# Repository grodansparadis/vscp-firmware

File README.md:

# VCSP Firmware

VSCP firmware contains examples for different hardware architectures of how to
implement the Very Simple Control Protocol (VSCP, [http://www.vscp.org](http://www.vscp.org)).

Shared VSCP firmware files reside in `/src`, while architecture-specific
common files reside in `/{arch}/common`.

Most important files for implementers are:

  * /src/vscp-firmware.* (for Level I nodes) and
  * /src/vscp-firmware-level2.* (for Level II (and Level I) nodes)

which both implements the VSCP protocol. The first alternative is created for very space limited devices, the second is for devices with more normal resources. 

There are also some references to
vscp_class.h and vscp_type.h which reside in the vscp_software repository
in the path /src/vscp/common. It is preferred to include these files from
that second repository (and not to make redundant copies if possible).

Documentation on how to build your own nodes from this code is [here](https://grodansparadis.github.io/vscp-doc-firmware/#/) 

Local module documentation for the helper library is available in [docs/vscp-firmware-helper.md](docs/vscp-firmware-helper.md).
Local module documentation for the VSCP FIFO helper is available in [docs/vscp-fifo.md](docs/vscp-fifo.md).
Local module documentation for the Level I firmware core is available in [docs/vscp-firmware.md](docs/vscp-firmware.md).
Local module documentation for the AES module is available in [docs/vscp-aes.md](docs/vscp-aes.md).
Local module documentation for the Level II firmware framework is available in [docs/vscp-firmware-level2.md](docs/vscp-firmware-level2.md).
Local module documentation for the VSCP link protocol is available in [docs/vscp-link-protocol.md](docs/vscp-link-protocol.md).
Local module documentation for serial protocol definitions is available in [docs/vscp-serial.md](docs/vscp-serial.md).
Local module documentation for the bootloader is available in [docs/vscp-bootloader.md](docs/vscp-bootloader.md).
Host-side firmware update flow for bootloader integration is available in [docs/vscp-bootloader-host-sequence.md](docs/vscp-bootloader-host-sequence.md).
Reusable VSCP link protocol callback bring-up checklist is available in [docs/examples/vscp-link-protocol-callback-checklist.md](docs/examples/vscp-link-protocol-callback-checklist.md).
Reusable VSCP Level I firmware porting checklist is available in [docs/examples/vscp-firmware-porting-checklist.md](docs/examples/vscp-firmware-porting-checklist.md).

## Recent updates

- Added `vscp_fwhlp_parseStringValue` behavior notes in [docs/vscp-firmware-helper.md](docs/vscp-firmware-helper.md), including base-prefix handling (`0x`, `0`, `0b`) and `endptr` token parsing semantics.

## Version

The library version is `year.month.patch` (for example `26.11.3`) and is in
[src/vscp-firmware-version.h](src/vscp-firmware-version.h):

- `VSCP_FIRMWARE_LIB_VERSION_YEAR`, `_MONTH`, `_PATCH` and `_STR`
- `VSCP_FIRMWARE_LIB_VERSION` as one number for compile time checks, e.g.
  `#if VSCP_FIRMWARE_LIB_VERSION >= VSCP_FIRMWARE_LIB_VERSION_CODE(26, 11, 3)`

It is updated automatically on every push to `master` by the
[Update version](https://github.com/grodansparadis/vscp-firmware/actions/workflows/update-version.yml)
workflow: the patch number counts the pushes in a month and starts at 0 in a
new month. Do not edit the header by hand. Pushes whose commit message
contains `[skip ci]` (anywhere, also in the body) do not change the version;
the workflow can also be started by hand from the Actions tab.

This is the version of the library code, not the VSCP protocol version that
nodes report in registers 0x81/0x82 (`VSCP_MAJOR_VERSION` etc. in
`vscp-firmware.h`).

## CI

- Tests workflow: [GitHub Actions - Tests](https://github.com/grodansparadis/vscp-firmware/actions/workflows/tests.yml)
- Version workflow: [GitHub Actions - Update version](https://github.com/grodansparadis/vscp-firmware/actions/workflows/update-version.yml)
- Latest workflow runs: [GitHub Actions runs](https://github.com/grodansparadis/vscp-firmware/actions)

The main reference implementations for VSCP over CAN is the Paris and the Kelvin modules. Both can found [here](http://www.grodansparadis.com/products.html) along with other open source products. All modules are available as 
ready made modules, bare pcb's and software and hardware is and will always be fully open and free. All design documents are open and available.

## License

The whole source code is published under the MIT license. Consider the different licenses of possible third party libraries too!

## Contribution

Unless you explicitly state otherwise, any contribution intentionally submitted for inclusion in the work by you, shall be licensed as above, without any additional terms or conditions.

Copyright 2000-2026 Ake Hedman <akhe@grodansparadis.com>, <a href="http://www.grodansparadis.com">Grodans Paradis AB</a>

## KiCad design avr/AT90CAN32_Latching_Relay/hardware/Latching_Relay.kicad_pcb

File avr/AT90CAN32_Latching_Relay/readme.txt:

This project implements a latchnig relay draive on an Atmega AT90CAN32 device. 

Pulse is sent after receiving Open (0x03) or Close (0x04) event.

Code is built using the GCC (AVR GCC) compiler.

Project configurations are done in the file vscp_projdefs.h  Also paths to include folders is 
in the Makefile and you probably have to change the paths.

If you port this project to use another compiler please use the vscp_compiler.h header to add 
compiler specific stuff. This file and the vscp_projdefs.h should be included in every file
of the project.

The mdf file describes the VSCP functionality.

SW0 - Init button. Press to initiate node and start nickname process.

LED0 - Status LED. Will blink during init process, stays steady on during operation.  

Serial channel, 38400-8N1 is used for debug messages.

Decision matrix is implemented.
No rows in the DM

Actions
=======
0x00 - No operation.

More information to be found at http://www.vscp.org/wiki/doku.php/modules/atmel_temp_humid

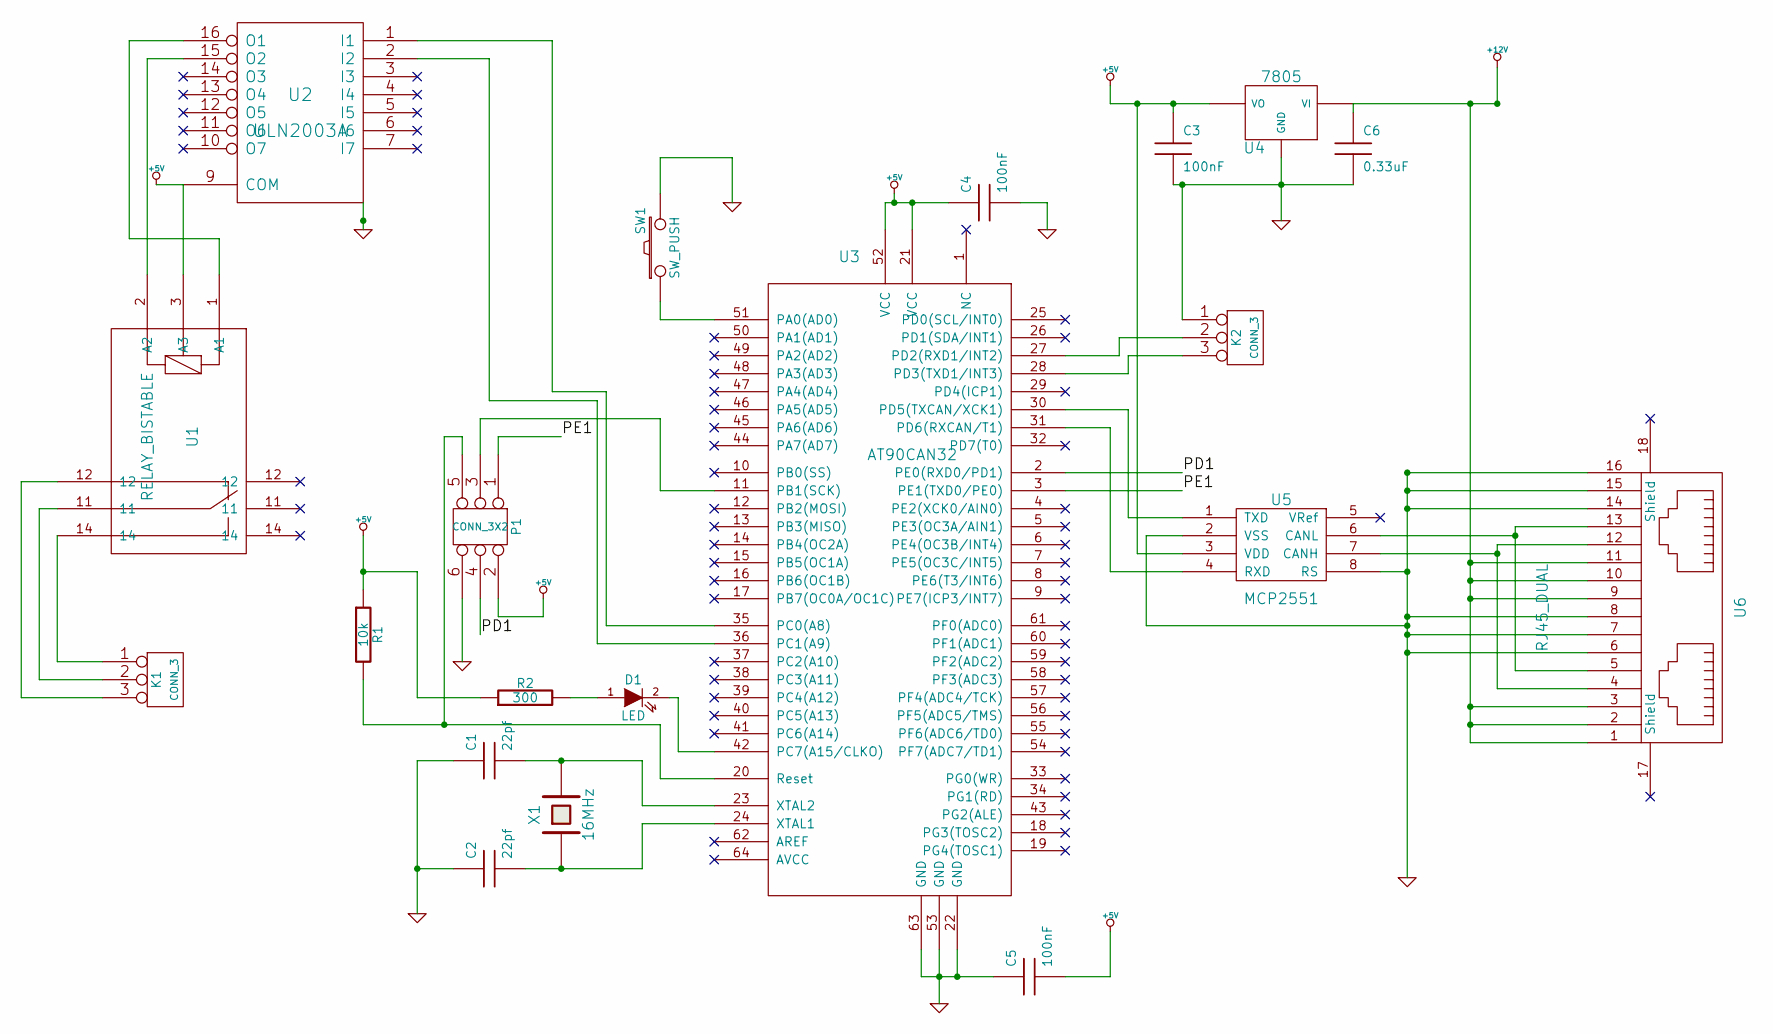
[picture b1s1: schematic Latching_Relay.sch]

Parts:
C1, C2: 22pf
C3, C4, C5: 100nF
C6: 0.33uF
D1: LED
K1, K2: CONN_3
P1: CONN_3X2
R1: 10k
R2: 300
SW1: SW_PUSH
U1: RELAY_BISTABLE
U2: ULN2003A
U3: AT90CAN32
U4: 7805
U5: MCP2551
U6: RJ45_DUAL
X1: 16MHz

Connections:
+5V: C3.1, C4.1, C5.2, P1.2, R1.1, R2.1, U1.3 (A3), U2.9 (COM), U3.21 (VCC), U3.52 (VCC), U4.3 (VO), U5.3 (VDD)
+12V: C6.1, U4.1 (VI), U6.1, U6.2, U6.3, U6.9, U6.10, U6.11
/PD1: P1.4, U3.2 (PE0(RXD0/PD1))
/PE1: P1.1, U3.3 (PE1(TXD0/PE0))
GND: C1.1, C2.1, C3.2, C4.2, C5.1, C6.2, K2.1, P1.6, SW1.2, U2.8 (GND), U3.22 (GND), U3.53 (GND), U3.63 (GND), U4.2 (GND), U5.2 (VSS), U5.8 (RS), U6.6, U6.7, U6.8, U6.14, U6.15, U6.16
unnamed: K2.2 (PM), U3.27 (PD2(RXD1/INT2))
unnamed: K2.3, U3.28 (PD3(TXD1/INT3))
unnamed: SW1.1, U3.51 (PA0(AD0))
unnamed: D1.2 (K), U3.42 (PC7(A15/CLKO))
unnamed: U3.30 (PD5(TXCAN/XCK1)), U5.1 (TXD)
unnamed: U3.31 (PD6(RXCAN/T1)), U5.4 (RXD)
unnamed: P1.3, U3.11 (PB1(SCK))
unnamed: P1.5, R1.2, U3.20 (Reset)
unnamed: U2.2 (I2), U3.36 (PC1(A9))
unnamed: U2.1 (I1), U3.35 (PC0(A8))
unnamed: K1.1, U1.14
unnamed: U1.1 (A1), U2.16 (O1)
unnamed: U1.2 (A2), U2.15 (O2)
unnamed: U5.6 (CANL), U6.5, U6.13
unnamed: U5.7 (CANH), U6.4, U6.12
unnamed: K1.3, U1.12
unnamed: K1.2 (PM), U1.11
unnamed: C1.2, U3.23 (XTAL2), X1.2
unnamed: C2.2, U3.24 (XTAL1), X1.1
unnamed: D1.1 (A), R2.2

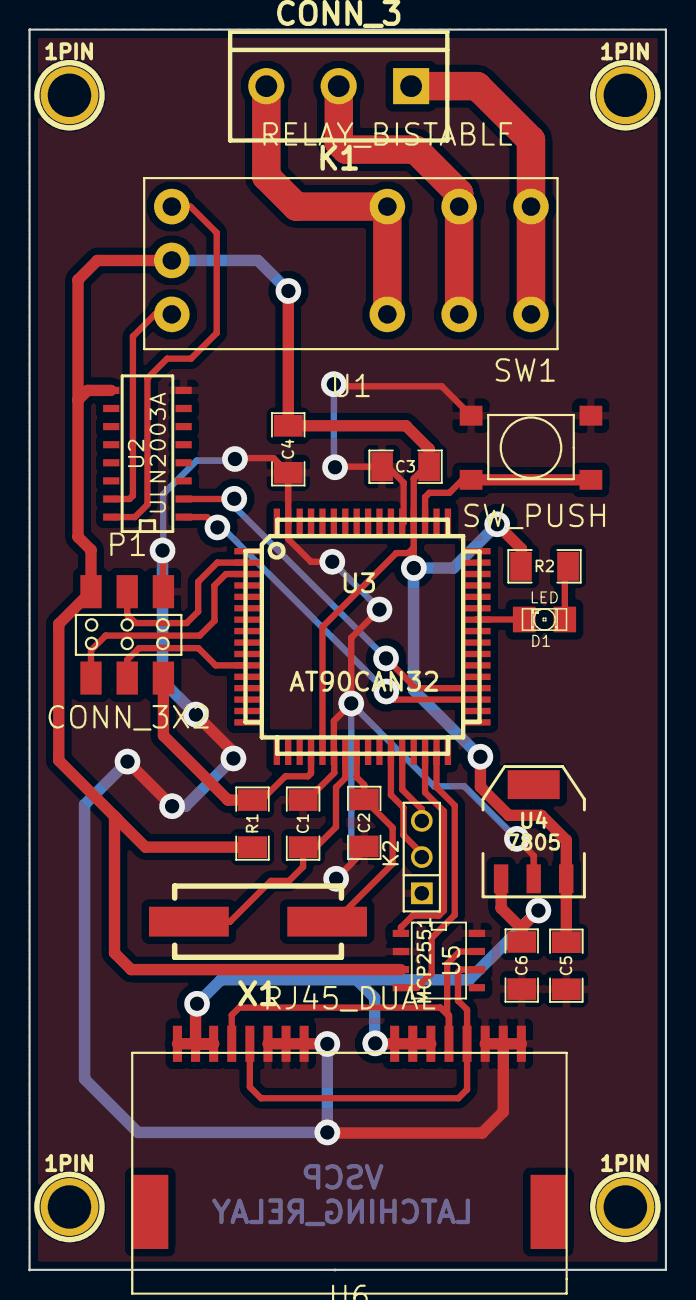
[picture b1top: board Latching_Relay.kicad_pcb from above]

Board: 2 copper layers, 44.7 x 87.1 mm, 24 parts (0 on the bottom side), 25 nets.

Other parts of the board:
1PIN, 1PIN#2, 1PIN#3, 1PIN#4: P***; 1pin

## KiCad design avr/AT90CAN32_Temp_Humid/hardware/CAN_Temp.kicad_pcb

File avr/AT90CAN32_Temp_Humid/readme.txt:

This project implements a temperature and a humidity sensor on an Atmega AT90CAN32device. 

Temperature and humidity are sent on a regular interval on the bus, the interval is set by the user using two registers.

Code is built using the GCC (AVR GCC) compiler.

Project configurations are done in the file vscp_projdefs.h  Also paths to include folders is 
in the Makefile and you probably have to change the paths.

If you port this project to use another compiler please use the vscp_compiler.h header to add 
compiler specific stuff. This file and the vscp_projdefs.h should be included in every file
of the project.

The mdf file describes the VSCP functionality.

SW0 - Init button. Press to initiate node and start nickname process.

LED0 - Status LED. Will blink during init process, stays steady on during operation.  

Serial channel, 38400-8N1 is used for debug messages.

Decision matrix is implemented.
No rows in the DM

Actions
=======
0x00 - No operation.

More information to be found at http://www.vscp.org/wiki/doku.php/modules/atmel_temp_humid

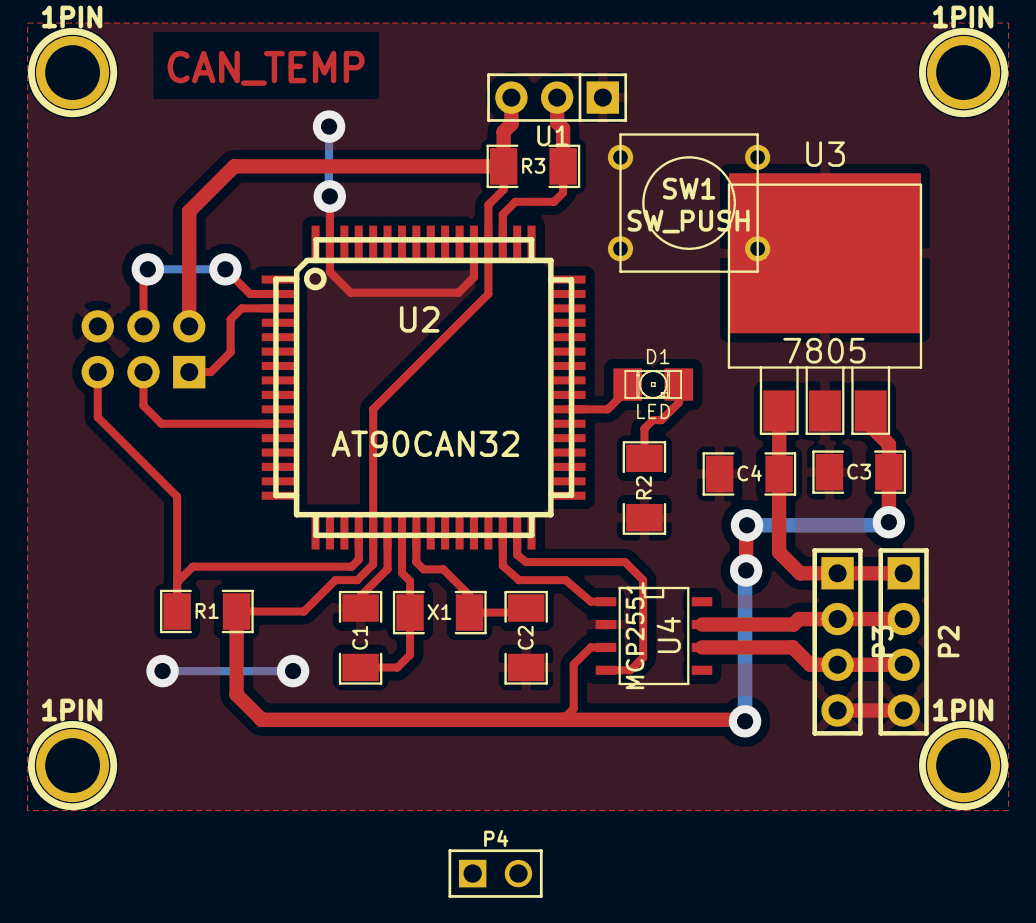
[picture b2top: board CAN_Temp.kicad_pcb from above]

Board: 2 copper layers, 22 parts (1 on the bottom side), 19 nets.

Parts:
1PIN, 1PIN#2, 1PIN#3, 1PIN#4: P***; 1pin
C1, C2: 22pf; SM1206
C3: 100nF; SM1206
C4: 0.33uF; SM1206
D1: LED; LED-1206
P1: CONN_3X2; pin_array_3x2
P2, P3: CONN_4; PIN_ARRAY_4x1
P4: CONN_2; PIN_ARRAY_2X1
R1: 10k; SM1206
R2: 300; SM1206
R3: 470k; SM1206
SW1: SW_PUSH; SW_PUSH_SMALL
U1: DS1820; PIN_ARRAY_3X1
U2: AT90CAN32; TQFP64_08
U3: 7805; DPAK3
U4: MCP2551; SO8E
X1: 16MHz; SM1206

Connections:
+5V: C3.1, P1.2, R1.1, R2.1, R3.1, U1.3, U2.21, U2.52, U3.3, U4.3
+12V: C4.1, P2.1, P3.1, U3.1
/PD1: P1.4, U2.2
/PE1: P1.1, U2.3
GND: C1.1, C2.1, C3.2, C4.2, P1.6, P2.4, P3.4, SW1.2, U1.1, U2.22, U2.53, U2.63, U3.2, U4.2, U4.8
unnamed: U2.30, U4.1
unnamed: U2.31, U4.4
unnamed: P1.3, U2.11
unnamed: P1.5, R1.2, U2.20
unnamed: P2.2, P3.2, U4.7
unnamed: P4.2, U2.28
unnamed: D1.2, R2.2
unnamed: P4.1, U2.27
unnamed: D1.1, U2.10
unnamed: R3.2, U1.2, U2.35
unnamed: SW1.1, U2.51
unnamed: P2.3, P3.3, U4.6
unnamed: C1.2, U2.23, X1.2
unnamed: C2.2, U2.24, X1.1

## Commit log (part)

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2015-03-23 Adding relay status register
2015-03-24 Cosmetics
2015-03-25 Preparing hardware
2015-04-01 Node now returns ON or OFF information event when state change instead of writing a register
2015-04-02 Fixed problem in read standard registers reported by Kim Portman. The device codes where at placed in thewrite routine instead of the read. Also a range check is done on mdf read suggested by Kim
2015-04-07 testing push from the office
2015-04-14 Change normalizer to fullfill latest change in WORKS
2015-04-15 Change vscp_goBootloaderMode() to fullfill latest change in WORKS
2015-05-21 Added CCITT CRC code
2015-05-21 Added crc8 routines Added fifo routines
2015-05-21 Added duplicates of critical files so there is no need to check out the full vscp_software repository. Needed for freertos work.
2015-05-21 Fixed some editing before IBM review
2015-05-22 commit before pull
2015-05-24 Synced with VSCP software - New classes CLASS1.ERROR/CLASS1.DIAGNOSTIC plus added event
2015-05-25 Anti-debounce for input
2015-05-25 Updated VSCP type copy
2015-05-28 Added support to PIC18F4580 and possibility of multiple BRG configuration selected using _XTAL_FREQ definition
2015-05-28 New projects
2015-05-28 Reverted class and type files that are just copies here.
2015-05-28 Spelling
2015-05-28 Restored missing files
2015-05-28 Trying to fix sendVSCPFrame
2015-06-11 Converted to new AVR studio
2015-06-12 Fixed extended read register response
2015-06-17 avr demo demo_vscp_node_can128 nw moved to avr studio
2015-06-17 Added link to demo hex
2015-06-17 changed the priority for packet bursts to the lowest priority (CAN == 111) so other frames win arbitration when they are sent. This will help other events moving on the bus.
2015-06-17 updated digiprobe project to compile with latest repository version
2015-07-09 Added VSCP_TYPE_DATA_COUNT
2015-09-10 Added
    Class=1060 (0x424) Measurement float
    and missing
    Class=1040 (0x410) Measurement string
2015-10-08 Added timstamp frames to serial protocol
2015-10-08 Added latest copy of common files
2015-10-14 cleanup
2015-10-20 Syncing headers
2015-10-21 Added CLASS2.PROTOCOL, Type=20 (0x14) High end server capabilities == synced with vscp repository
2015-10-26 Added 128-bit AES tiny code
2015-11-03 Synced includes
2015-11-09 Added code to read chip id on pic18
2015-11-25 Rolled back vscp_firmware.c/h from some happy hacking ;-) @SvenZ80
2015-11-25 Added macros to construct signed integers from EEPROM content in a safe c standard way.
2016-01-07 Removed segment check
2016-01-29 Fixed trillons of TAB's
2016-01-29 Added some untracked stuff
2016-02-03 Changed avr_can128 sample so it works with latest firmware
2016-02-03 Rnemamed local inttypes.h vscp_inttypes.h *** This file is usually not needed anymore ***
2016-02-04 Added initial lib for AVR1 bootloader
2016-02-07 New bootloader implemention for AVR
2016-02-07 Fixed problem in 32-bit macros
2016-02-12 Syncing
2016-03-02 Made work in progress firmware intrim. usable
2016-03-18 Added new internal calculation event
2016-03-23 Added error event and logger event
2016-03-23 Added history file to keep track of changes from now on
2016-03-23 Release 1.6.1
2016-09-06 update
    methods.c/.h updated to remain compatible with common/vscp_firmware.h
2016-09-06 avoid bus flooding
    added timer to avoid to dump to much events on bus
2016-12-09 rollout 2016
2016-12-29 Added event for sound level and sound pressure
2016-12-29 Synced types
2017-01-22 8bit -> 16bit eeprom adress
    bug preventing to read/write more than 128 eeprom locations
2017-01-22 add nickname accepted after setnickname event
    upp untik now, no response was send after setnickname event
2017-01-24 Sync with main
2017-02-02 aaboot
2017-02-02 cleaning up
2017-02-17 bootloader now works according to vscp-algorithm
    used to test bootloader firmware.
2017-02-17 added MDF
2017-04-05 HW-upgrade AAMEGA
    AAMEGA now has 32 output (instead of 16) with added piggyback-board
2017-04-13 The VSCP frame now have a full date/time field. Code that relay on the struct size must be recompiled.
2017-04-18 VSCP structure and frame now have a date/time block.
2017-05-08 Synced with the VSCP project
2017-06-13 Updated mu.ticast/udp constants
2017-06-14 USP and multicast frames was missing the century byte of the year.
2017-06-25 Updated to latest upstream version
2017-07-04 coap and mqtt removed fom capabilities word
2017-07-04 multicast moved
2017-07-11 vscpEvenEx had wrong size for head
2017-09-07 debug timerroutine
    only timer could be used from DM
2017-09-07 minor cleanup
2017-11-10 small update
    tweaked some timing: slower but more reliable
2017-11-10 shutters added
    added action-routines to drive shutter/blinds/...
2018-02-09 Sunced files with main
2018-02-19 Started work with Level II firmware
2018-02-19 improve shutter code after real life-test + add fixed actions
2018-03-14 Bugfix by Andy
2018-04-19 Syncing with main code
2018-07-09 Updated autogenerated files
2018-10-18 sync
2018-10-31 Added prototypes for link
2018-11-28 Syncing VSCP errors and events
2019-01-11 Update copyright
2019-01-11 Sync from autogeneration
2020-01-02 Updated copyright
2020-05-05 vscp_initbtncnt increased to 16-bit
2020-05-05 Samples and external contributions moved to contrib folder
2020-05-08 Fixed problem with include header different from source
2020-05-08 Added changelog
2021-10-21 Updated funding info
2022-01-23 Added handling of firmware code added i spec 1.13.
2022-02-07 Added data count before "Who is there response"
2022-04-27 Removed old files
2022-04-27 Renamed files
2022-05-05 Added user data to tcp/ip link handlers
2022-05-06 Added clang format config
2022-05-19 Fixed return type for a2ul to confirm to other returns
2022-05-19 Added fifo handler for VSCP events
2022-05-20 Removed obsolete vscp-server code
2022-05-23 Upated vscp class/type defs
2022-06-02 Removed some unused files
2022-06-02 Removed unused stuff
2022-09-14 Removed unused code
2022-12-07 Added AES encyption/decryption to helper
2022-12-07 Added files for AES encryption/decryption (copy from main vscp project)
2023-01-09 Updated copyright year
2023-01-26 Rnemaed AES files
2023-02-09 Firmware Link protocol fully implemented
2023-04-05 Updated to latest version of vscp.h
2023-04-05 Moved new vscp.h to the correct location
2023-04-19 Updated classes/types to latest
2023-05-04 Changed names on defines to make usaage clearer
2023-05-04 Made link config defines for projdef clearer
2023-05-08 Espressif biit algotithm added
2023-05-08 Synced vscp.h with main project (VSCP_STD_REGISTER_NODE_RESET)
2023-05-12 Memmory allocation mnacros removed
2024-05-13 vscp_type-h and vscp_class.h renamed to vscp-type.h and vscp-class.h as part of general change
2024-05-17 All level II code in place but not tested
2024-05-24 Fixed config
2024-06-20 Fixed som bugs after test
2024-06-25 Fixed construct_unsigned32 and construct_signed32 macros
2024-09-10 Fixed problem with MDF URL reading
2024-09-17 vscp header updated to latest version
2024-10-23 Changed timestamp callback return to 64 bit
2024-10-24 cJSON is now a submodule
2024-10-24 Added JSON helpers for event ex
2024-10-30 Added pointer checks to json event parsers and generators
2024-10-31 Added some info about level II code
2024-11-01 Added new level II classes
2024-11-22 Enter bootloader now give negative response on wrong data
2024-12-12 VSCP bootloader device code in a "working" state
2025-01-12 Fixed some warnings
2025-01-15 Updated class/type references
2025-01-19 Updated class/types
2025-02-14 Fixed some paths that could result in uninitialized vars
2025-02-20 Commands now can handle wgitespace at front and at end
2025-02-20 Added interface command help
2025-02-21 Fixed problem when reading octal string value
2025-02-21 Added link to docs
2025-02-23 Fixed missnamed methods
2025-02-27 Fixed error in function description
2025-04-28 Fixed VSCP string parsing to accept undefined obid, timstamp and date (set to defaults)
2025-04-29 Fixed bugs introduced from move from vscp main code
2025-05-07 Updated imported headers to latest version
2025-05-07 Fixed missing includes
2025-09-02 Fixed #14
2025-09-19 Rearranged configuration parameters
2026-01-27 Updated duplicat vscp.h with timestamp change
2026-02-03 Added c++ protection
2026-02-03 Fixed copyright year
2026-02-12 Added check for parser result
2026-02-13 Fixed buffer overflow
2026-02-13 Fixed memory error
2026-02-15 Added xml parser submodule
2026-02-16 Added ns timestamp conversions
2026-02-16 Added datestring coonversions
2026-02-19 Added workflow for tests
2026-02-19 Removed cJSON dependency from test
2026-02-19 Added submodule checkout
2026-02-19 Removed c++ code that should not be there
2026-02-19 Fixed erronoius comment
2026-02-19 Fixed signed char problem
2026-02-19 Added test cases for event tags and made expected format more strict
2026-02-19 Added missing XML conversion
2026-02-20 Added MQTT topic parsers for GUID, class and type
2026-02-20 Added missing measurement functions
2026-02-20 Added stdbool.h for false/true usage
2026-02-20 Removed dependency on stdbool.h
2026-02-23 Renamed VSCP str event parsers
2026-02-23 Name change of parse string to event also in vscp-link-protocol file
2026-02-24 Added tests for event string parsers
2026-02-24 Fixed test so it works with gcc also
2026-03-05 Updated to latest vscp header copy
2026-03-10 Added vscp_fwhlp_writeFilterToString and vscp_fwhlp_writeMaskToString
2026-03-12 Added parsers for the extended GUID format
2026-03-12 Replaced GUID parser with new version and added new renders fro GUID
2026-03-13 Change vscp_fwhlp_a2ul and vscp_fwhlp_readStringValue to return 64-bit integers
2026-03-13 Always produce frame version 1 (nanosecond timestamp) for string serialization
    - parseStringToEvent/Ex: Convert datetime+microseconds to nanoseconds
    - eventToString/Ex: Always output nanosecond timestamp format
    - Updated tests to reflect new behavior
2026-03-13 Add comprehensive tests for vscp_fwhlp_parseStringValue uint64_t
2026-03-13 Fix C compilation: add stdbool.h include and replace nullptr with NULL
2026-03-17 VSCP_FWHLP_UDP_FRAME_SUPPORT changed to VSCP_FWHLP_BINARY_FRAME_SUPPORT for consistancy
2026-03-17 Added binary frame helpers vscp_fwhlp_writeCommandToFrame and vscp_fwhlp_writeReplyToFrame
2026-03-17 Updated vscp.h to latest
2026-03-20 Revert to previous build
2026-03-22 made data input const
2026-03-25 Conversion to new frame format when rading binary frame
2026-03-25 Added the year/month makers for a converted fram
2026-03-26 vscp_interface_info_t moved to vscp.h
2026-04-07 Updated comments
2026-04-08 Using new typedef for events. esp32 now uses hardware encryption
2026-04-08 Updated event defs to use new typedef
2026-04-09 Openssl option introduces for encryption/decryption
2026-04-09 crc.h/crc.c is renamed to vscp-crc.h/vscp-crc-c
2026-04-09 Fix gtest crcTable linkage and clean CRC macro warnings
2026-04-09 JSON parser now can handle both current and legacy format
2026-06-10 Added vscp_fifo_deinit for completeness
2026-06-10 Added missing header
2026-06-10 Increased default in/out buffers
2026-06-11 Changed vscp-link-protocol to have table based callback mechanism
2026-06-11 Removed last changed in readme
2026-06-11 Renamed files for consistancy
2026-06-11 Fixed tests op they work with the new naming
2026-06-17 Added user pointer to firmware 2 context struct
2026-06-17 Adopted tests for simplified link parser
2026-06-17 Added protections around context pointer
2026-06-17 Changed all vscp_event_ex_t to vscp_event_t
2026-06-17 Removed some hardcoded literals
2026-06-18 Refactored
2026-06-18 Added callback header for level 2 firmware
2026-06-23 Fix: Event string rendering
    %llu not supported on many platforms. Now using two halves and %lu%09lu
2026-06-23 Corrected format
2026-06-23 Now using dynamic event alloction
2026-06-25 FIX: Removed missnamed callbacks
2026-06-25 Updated translations
2026-06-25 FIX: Changed type for user reg variable, rename family
2026-06-28 Added bits for status
2026-06-29 Changed GUID init

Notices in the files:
README.md:
License: MIT
